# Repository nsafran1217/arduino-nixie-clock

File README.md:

# arduino-nixie-clock
Custom IN-12A (ИН-12А) Nixie clock with RTC and arduino

This code is messy and specific to my board design. 

I made one change after recieving the boards. I needed a 5volt power pin for the rotary encoder. I scrapped up a trace to a digital pin on the button header and added a bodge wire for 5 volts. You will need to get 5v to your rotary encoder

https://www.amazon.com/HiLetgo-Degrees-Rotary-Encoder-Arduino/dp/B07WZF1TXX/ref=sr_1_9?crid=1PWJRHJRPVXBX&dchild=1&keywords=rotary+encoder&qid=1586055969&sprefix=rotary+e%2Caps%2C135&sr=8-9

# Main Modes
Adjust by turning rotary encoder
* 0: Time mode
* 1: Date mode
* 2: Rotate mode

Rotate mode rotates between date and time at a set interval

# Settings menu
Enter settings menu by pressing rotary encoder

Press it again to change the selected setting

* 0: Exit settings menu
* 1: Set Time
* 2: Set Date
* 3: Set rotation interval in seconds
* 4: Select 12 or 24 hour display
* 5: Set the time transition mode. currently there is only two. 0 for normal and 1 for slot machine effect.
* 6: Set time to turn display off then back on. First digit is the hour it turns off. second is the hour it turns back on
* 7: Set anti cathode poison time. Fist digit is the minute that the first run will happen on. Second is the interval in minutes that it runs

example: 15 - 10. the first run will happen at 0:15 and the next run will happen at 0:25. Add 10 minutes for every run after

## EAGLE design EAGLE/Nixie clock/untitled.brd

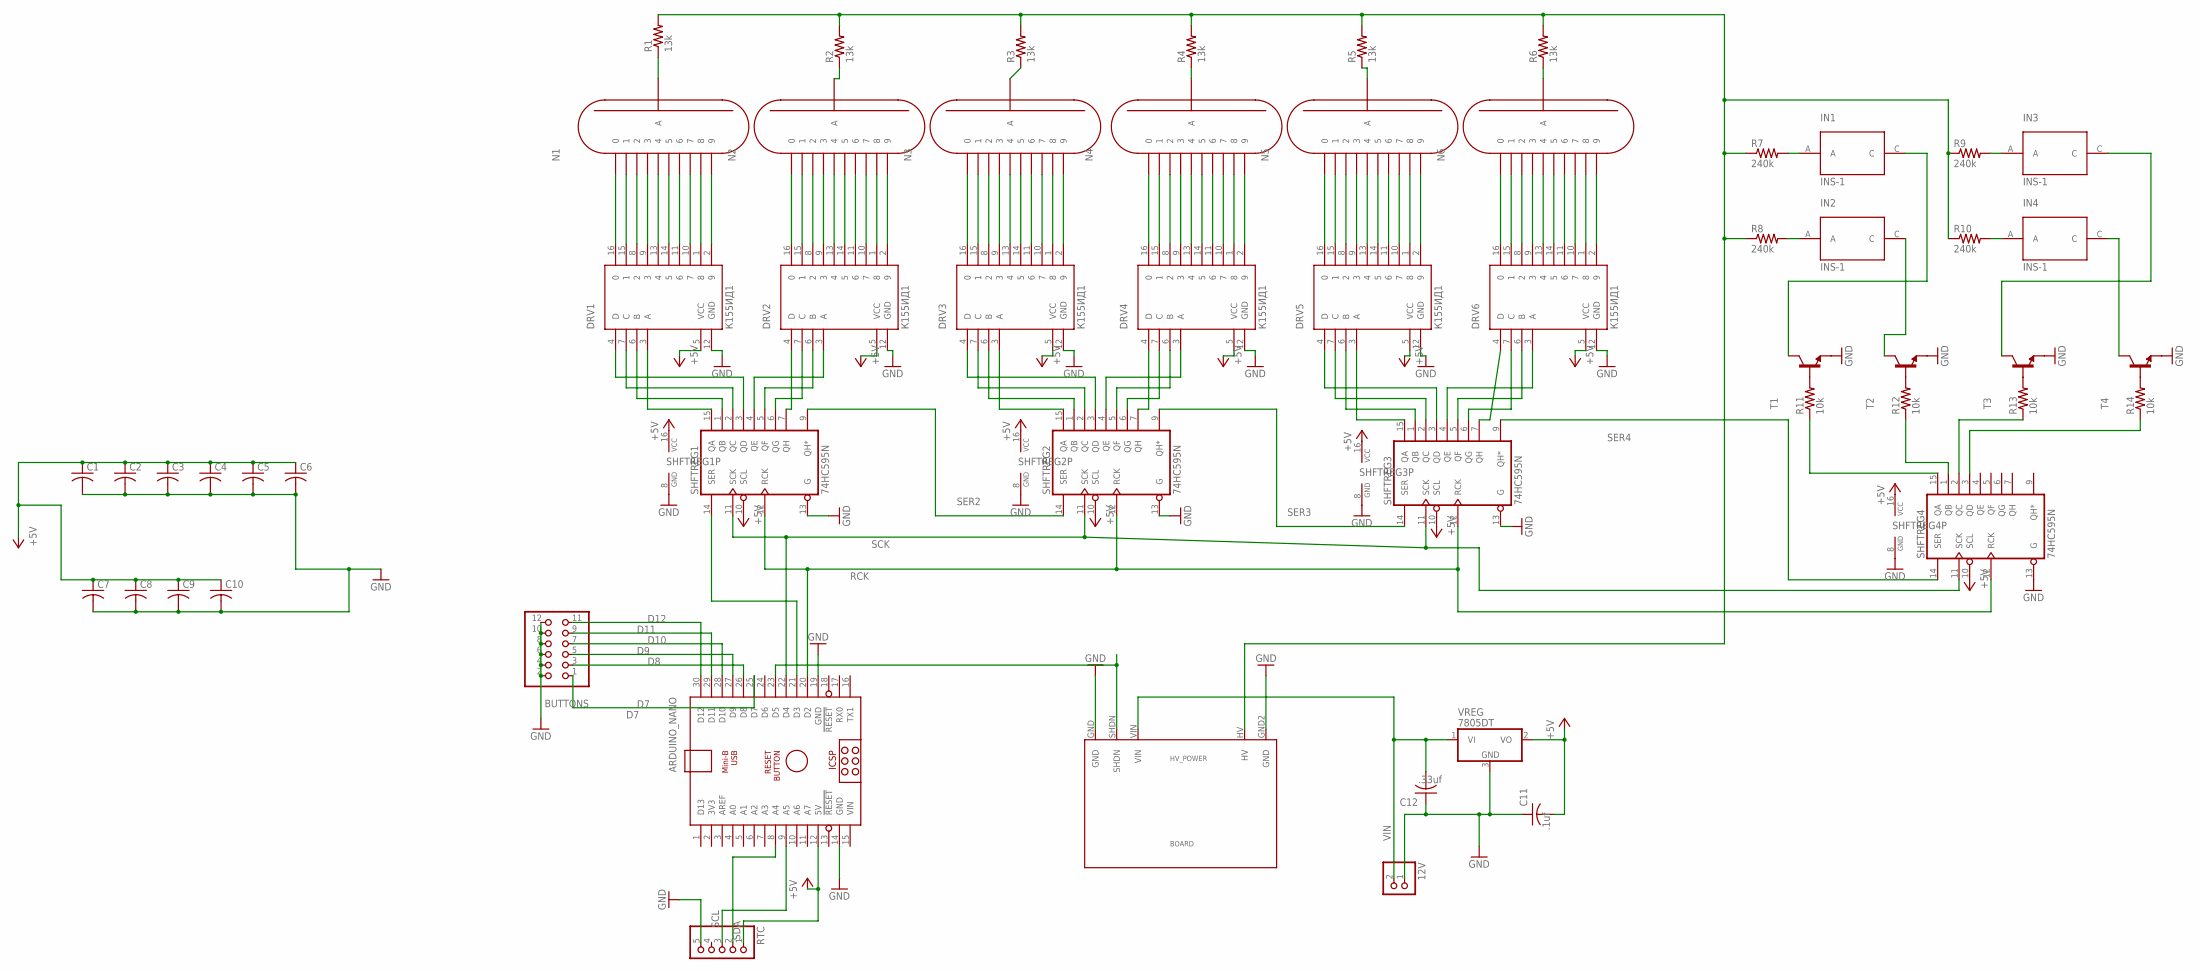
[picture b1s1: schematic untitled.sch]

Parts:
12V: PINHD-1X2/90; 1X02/90
ARDUINO_NANO: ARDUINO_NANO
BUTTONS: PINHD-2X6/90; 2X06/90
C1, C2, C3, C4, C5, C6, C7, C8, C9, C10: C-USC0805; C0805
C11: .1uf; C0805
C12: .33uf; C0805
DRV1, DRV2, DRV3, DRV4, DRV5, DRV6: К155ИД1; DIL16
HV_POWER: BOARD
IN1, IN2, IN3, IN4: INS-1
N1, N2, N3, N4, N5, N6: IN-12A; IN-12
R1, R2, R3, R4, R5, R6: 13k; R0805
R7, R8, R9, R10: 240k; R0805
R11, R12, R13, R14: 10k; R0805
RTC: PINHD-1X5; 1X05
SHFTREG1, SHFTREG2, SHFTREG3, SHFTREG4: 74HC595N; DIL16
T1, T2, T3, T4: MMBTA42LT1-NPN-SOT23-BEC; SOT23-BEC
VREG: 7805DT; TO252

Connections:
+5V: ARDUINO_NANO.12 (5V), C1.1, C2.1, C3.1, C4.1, C5.1, C6.1, C7.1, C8.1, C9.1, C10.1, C11.2, DRV1.5 (VCC), DRV2.5 (VCC), DRV3.5 (VCC), DRV4.5 (VCC), DRV5.5 (VCC), DRV6.5 (VCC), RTC.1, SHFTREG1.10 (SCL), SHFTREG1.16 (VCC), SHFTREG2.10 (SCL), SHFTREG2.16 (VCC), SHFTREG3.10 (SCL), SHFTREG3.16 (VCC), SHFTREG4.10 (SCL), SHFTREG4.16 (VCC), VREG.2 (VO)
D7: ARDUINO_NANO.25 (D7), BUTTONS.1
D8: ARDUINO_NANO.26 (D8), BUTTONS.3
D9: ARDUINO_NANO.27 (D9), BUTTONS.5
D10: ARDUINO_NANO.28 (D10), BUTTONS.7
D11: ARDUINO_NANO.29 (D11), BUTTONS.9
D12: ARDUINO_NANO.30 (D12), BUTTONS.11
GND: 12V.1, ARDUINO_NANO.14 (GND), ARDUINO_NANO.19 (GND), BUTTONS.2, BUTTONS.4, BUTTONS.6, BUTTONS.8, BUTTONS.10, BUTTONS.12, C1.2, C2.2, C3.2, C4.2, C5.2, C6.2, C7.2, C8.2, C9.2, C10.2, C11.1, C12.1, DRV1.12 (GND), DRV2.12 (GND), DRV3.12 (GND), DRV4.12 (GND), DRV5.12 (GND), DRV6.12 (GND), HV_POWER.GND, HV_POWER.GND2 (GND), RTC.5, SHFTREG1.8 (GND), SHFTREG1.13 (G), SHFTREG2.8 (GND), SHFTREG2.13 (G), SHFTREG3.8 (GND), SHFTREG3.13 (G), SHFTREG4.8 (GND), SHFTREG4.13 (G), T1.E, T2.E, T3.E, T4.E, VREG.3 (GND)
unnamed: DRV4.4 (D), SHFTREG2.7 (QH)
unnamed: DRV1.16 (0), N1.0
unnamed: DRV1.15 (1), N1.1
unnamed: DRV1.8 (2), N1.2
unnamed: DRV1.9 (3), N1.3
unnamed: DRV1.13 (4), N1.4
unnamed: DRV1.11 (6), N1.6
unnamed: DRV1.14 (5), N1.5
unnamed: DRV1.10 (7), N1.7
unnamed: DRV1.1 (8), N1.8
unnamed: DRV1.2 (9), N1.9
unnamed: DRV2.16 (0), N2.0
unnamed: DRV2.15 (1), N2.1
unnamed: DRV2.8 (2), N2.2
unnamed: DRV2.9 (3), N2.3
unnamed: DRV2.13 (4), N2.4
unnamed: DRV2.14 (5), N2.5
unnamed: DRV2.11 (6), N2.6
unnamed: DRV2.10 (7), N2.7
unnamed: DRV2.1 (8), N2.8
unnamed: DRV2.2 (9), N2.9
unnamed: DRV3.16 (0), N3.0
unnamed: DRV3.15 (1), N3.1
unnamed: DRV3.8 (2), N3.2
unnamed: DRV3.9 (3), N3.3
unnamed: DRV3.13 (4), N3.4
unnamed: DRV3.14 (5), N3.5
unnamed: DRV3.11 (6), N3.6
unnamed: DRV3.10 (7), N3.7
unnamed: DRV3.1 (8), N3.8
unnamed: DRV3.2 (9), N3.9
unnamed: DRV4.16 (0), N4.0
unnamed: DRV4.15 (1), N4.1
unnamed: DRV4.8 (2), N4.2
unnamed: DRV4.9 (3), N4.3
unnamed: DRV4.13 (4), N4.4
unnamed: DRV4.14 (5), N4.5
unnamed: DRV4.11 (6), N4.6
unnamed: DRV4.10 (7), N4.7
unnamed: DRV4.1 (8), N4.8
unnamed: DRV4.2 (9), N4.9
unnamed: DRV5.16 (0), N5.0
unnamed: DRV5.15 (1), N5.1
unnamed: DRV5.8 (2), N5.2
unnamed: DRV5.9 (3), N5.3
unnamed: DRV5.13 (4), N5.4
unnamed: DRV5.11 (6), N5.6
unnamed: DRV5.14 (5), N5.5
unnamed: DRV5.10 (7), N5.7
unnamed: DRV5.1 (8), N5.8
unnamed: DRV5.2 (9), N5.9
unnamed: DRV6.16 (0), N6.0
unnamed: DRV6.15 (1), N6.1
unnamed: DRV6.8 (2), N6.2
unnamed: DRV6.9 (3), N6.3
unnamed: DRV6.13 (4), N6.4
unnamed: DRV6.14 (5), N6.5
unnamed: DRV6.11 (6), N6.6
unnamed: DRV6.10 (7), N6.7
unnamed: DRV6.1 (8), N6.8
unnamed: DRV1.3 (A), SHFTREG1.15 (QA)
unnamed: DRV1.6 (B), SHFTREG1.1 (QB)
unnamed: DRV1.7 (C), SHFTREG1.2 (QC)
unnamed: DRV1.4 (D), SHFTREG1.3 (QD)
unnamed: DRV2.3 (A), SHFTREG1.4 (QE)
unnamed: DRV2.6 (B), SHFTREG1.5 (QF)
unnamed: DRV2.7 (C), SHFTREG1.6 (QG)
unnamed: DRV2.4 (D), SHFTREG1.7 (QH)
unnamed: ARDUINO_NANO.23 (D5), HV_POWER.SHDN
unnamed: DRV3.3 (A), SHFTREG2.15 (QA)
unnamed: DRV3.6 (B), SHFTREG2.1 (QB)
unnamed: DRV3.7 (C), SHFTREG2.2 (QC)
unnamed: DRV3.4 (D), SHFTREG2.3 (QD)
unnamed: DRV4.3 (A), SHFTREG2.4 (QE)
unnamed: DRV4.6 (B), SHFTREG2.5 (QF)
unnamed: DRV4.7 (C), SHFTREG2.6 (QG)
unnamed: DRV6.2 (9), N6.9
unnamed: DRV5.3 (A), SHFTREG3.15 (QA)
unnamed: DRV5.6 (B), SHFTREG3.1 (QB)
unnamed: DRV5.7 (C), SHFTREG3.2 (QC)
unnamed: DRV5.4 (D), SHFTREG3.3 (QD)
unnamed: DRV6.3 (A), SHFTREG3.4 (QE)
unnamed: DRV6.6 (B), SHFTREG3.5 (QF)
unnamed: DRV6.7 (C), SHFTREG3.6 (QG)
unnamed: DRV6.4 (D), SHFTREG3.7 (QH)
unnamed: IN1.C, T1.C
unnamed: N1.A, R1.1
unnamed: N2.A, R2.1
unnamed: N3.A, R3.1
unnamed: N4.A, R4.1
unnamed: N5.A, R5.1
unnamed: N6.A, R6.1
unnamed: IN2.A, R8.2
unnamed: IN1.A, R7.2
unnamed: IN3.A, R9.2
unnamed: IN4.A, R10.2
unnamed: HV_POWER.HV, R1.2, R2.2, R3.2, R4.2, R5.2, R6.2, R7.1, R8.1, R9.1, R10.1
unnamed: R11.2, T1.B
unnamed: R12.2, T2.B
unnamed: R13.2, T3.B
unnamed: R11.1, SHFTREG4.15 (QA)
unnamed: R12.1, SHFTREG4.1 (QB)
unnamed: IN3.C, T3.C
unnamed: R13.1, SHFTREG4.2 (QC)
unnamed: R14.1, SHFTREG4.3 (QD)
unnamed: IN4.C, T4.C
unnamed: R14.2, T4.B
unnamed: IN2.C, T2.C
RCK: ARDUINO_NANO.20 (D2), SHFTREG1.12 (RCK), SHFTREG2.12 (RCK), SHFTREG3.12 (RCK), SHFTREG4.12 (RCK)
SCK: ARDUINO_NANO.22 (D4), SHFTREG1.11 (SCK), SHFTREG2.11 (SCK), SHFTREG3.11 (SCK), SHFTREG4.11 (SCK)
SCL: ARDUINO_NANO.9 (A5), RTC.3
SDA: ARDUINO_NANO.8 (A4), RTC.2
SER1: ARDUINO_NANO.21 (D3), SHFTREG1.14 (SER)
SER2: SHFTREG1.9 (QH*), SHFTREG2.14 (SER)
SER3: SHFTREG2.9 (QH*), SHFTREG3.14 (SER)
SER4: SHFTREG3.9 (QH*), SHFTREG4.14 (SER)
VIN: 12V.2, ARDUINO_NANO.15 (VIN), C12.2, HV_POWER.VIN, VREG.1 (VI)

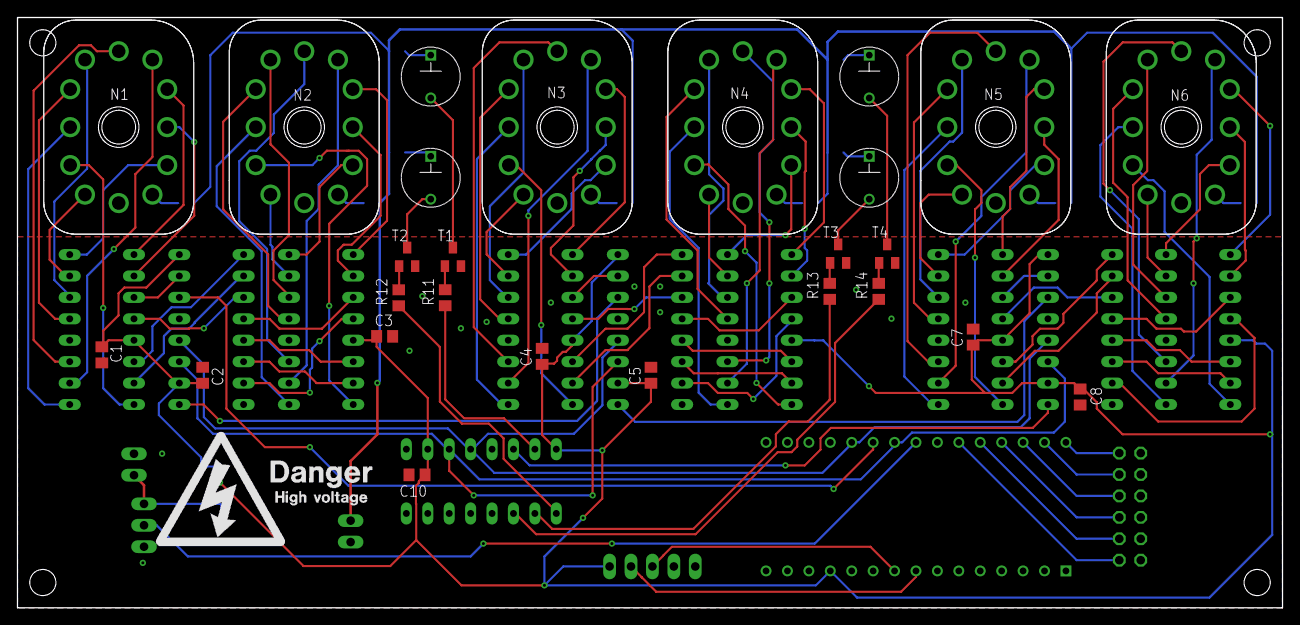
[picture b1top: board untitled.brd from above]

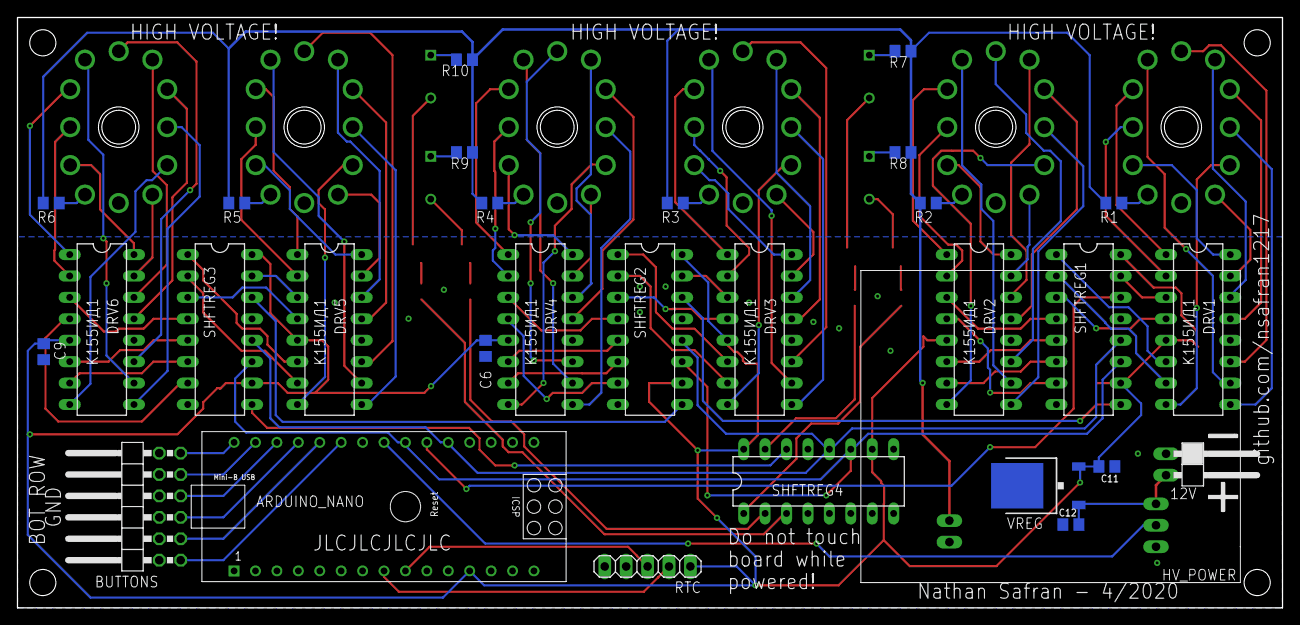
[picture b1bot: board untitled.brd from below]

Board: 2 copper layers, 150.0 x 70.0 mm, 57 parts (30 on the bottom side), 125 nets.

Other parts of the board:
U$1: HV

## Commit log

2020-04-02 just before removing button, rotary is in it.
2020-04-04 still working on transition modes
2020-04-04 scroll function finished and ugly
2020-04-04 added eagle design files
2020-04-05 I think its done
2020-04-05 adding pictures, fixing small bugs
